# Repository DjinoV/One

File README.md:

# One
 A tiny model rocket flight computer and data logger.
 
 It features:
 - A STM32F103C8T6
 - A BMI088 IMU
 - A BMP280 Barometric pressure sensor
 - A microSD card slot
 - A 32MB flash chip
 - A single pyro channel 
 - Micro USB
 - And ofcourse, a single RGB LED

 Board size:
 50(maybe 40)x30mm
 Powered off a 12V Li-Po

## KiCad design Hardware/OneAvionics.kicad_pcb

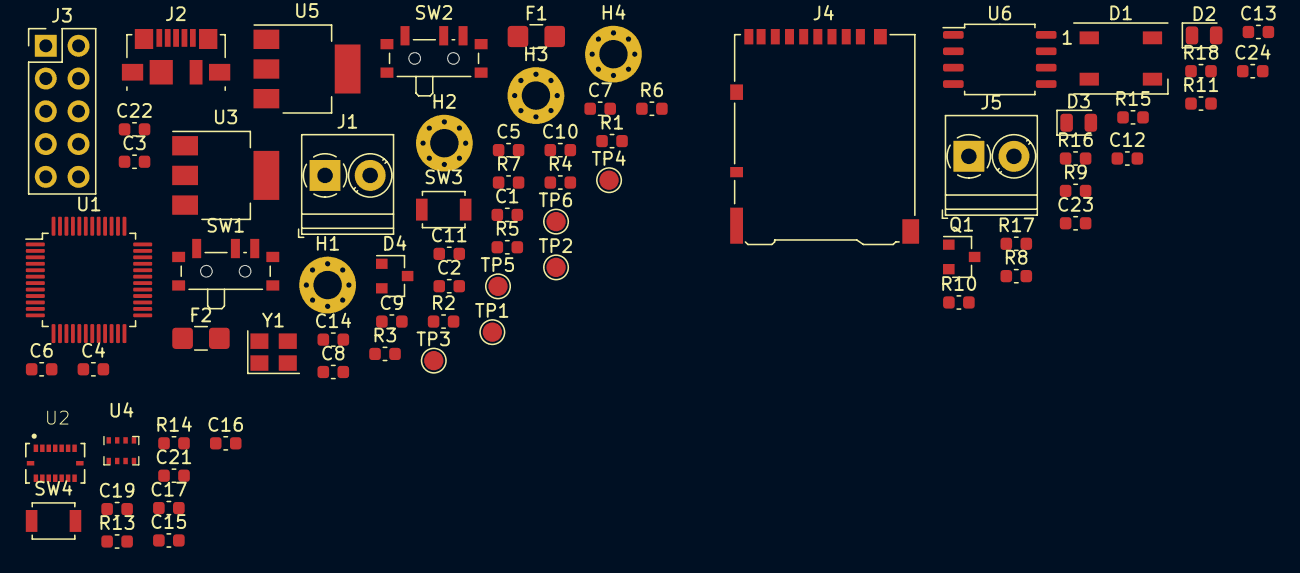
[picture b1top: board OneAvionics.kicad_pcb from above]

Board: 2 copper layers, 72 parts (0 on the bottom side), 37 nets, no tracks yet.

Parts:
C1, C2, C3, C4, C5, C6, C7, C12, C13, C15, C16, C17, C19, C21, C24: 100nF; C_0603_1608Metric
C8, C14: 10uF; C_0603_1608Metric
C9, C22: 0.1uF; C_0603_1608Metric
C10, C11: 22pF; C_0603_1608Metric
C23: 470uF; C_0603_1608Metric
D1: WS2812B; LED_WS2812B_PLCC4_5.0x5.0mm_P3.2mm
D2, D3: LED; LED_0805_2012Metric
D4: D_Schottky; SOT-23
F1, F2: 2A; Fuse_1206_3216Metric_Castellated
H1, H2, H3, H4: MountingHole; MountingHole_2.2mm_M2_Pad_Via
J1: Conn_01x02; TerminalBlock_Phoenix_PT-1,5-2-3.5-H_1x02_P3.50mm_Horizontal
J2: USB_B_Micro; USB_Micro-B_Molex_47346-0001
J3: SWD; PinHeader_2x05_P2.54mm_Vertical
J4: Micro_SD_Card; microSD_HC_Hirose_DM3AT-SF-PEJM5
J5: ST_01x02; TerminalBlock_Phoenix_PT-1,5-2-3.5-H_1x02_P3.50mm_Horizontal
Q1: DMN2230U; SOT-23
R1, R2, R7, R9, R13, R14: 10K; C_0603_1608Metric
R3, R6: 22R; C_0603_1608Metric
R4, R17: 100K; C_0603_1608Metric
R5: 38K; C_0603_1608Metric
R8, R10, R11: 150R; C_0603_1608Metric
R15: 200R; C_0603_1608Metric
R16: 5R; C_0603_1608Metric
R18: 20K; C_0603_1608Metric
SW1, SW2: SW_SPDT; SW_SPDT_PCM12
SW3, SW4: SW_Push; SW_SPST_B3U-1000P
TP1, TP2, TP3, TP4, TP5, TP6: TestPoint; TestPoint_Pad_D1.5mm
U1: STM32F103C8Tx; LQFP-48_7x7mm_P0.5mm
U2: BMI088; PQFN50P450X300X100-16N
U3, U5: LM1117-3.3; SOT-223
U4: BMP280; Bosch_LGA-8_2x2.5mm_P0.65mm_ClockwisePinNumbering
U6: W25Q32JVSS; SOIC-8_5.23x5.23mm_P1.27mm
Y1: 16MHz; Crystal_SMD_3225-4Pin_3.2x2.5mm

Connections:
+3V3: C3.1, C4.1, C5.1, C6.1, C7.1, C9.2, C12.2, C13.2, C15.2, C16.1, C17.2, C19.2, C22.2, C24.2, D1.1, J3.1, J4.4, R7.1, R10.2, R13.1, R14.1, SW1.1, TP3.1, U1.1, U1.9, U1.24, U1.36, U1.48, U2.3, U2.7, U2.11, U2.14, U3.2, U4.2, U4.6, U4.8, U5.2, U6.8
+5V: C1.2, F2.2, J2.1, TP4.1
+12V: F1.2, R4.2, R15.2, SW2.1
/BOOT0: R1.2, TP5.1, U1.44
/BOOT1: R2.2, TP2.1, U1.20
/BUTTON: C21.1, SW4.1, U1.13
/D+: R3.1, U1.32
/D-: R6.1, U1.33
/HSE_IN: C10.1, U1.5, Y1.1
/HSE_OUT: C11.1, U1.6, Y1.3
/LED: R11.2, U1.12
/MISO: J4.7, U1.16, U6.2
/MOSI: J4.3, U1.17, U6.5
/NRST: C2.1, J3.10, R7.2, SW3.1, TP1.1, U1.7
/Output/PYRO_CONT: R17.2, R18.1
/PYRO_1: R8.2, U1.28
/RGB: D1.4, U1.27
/SCK: J4.5, U1.15, U6.6
/SCL: R14.2, U1.42, U2.8, U4.4
/SDA: R13.2, U1.43, U2.9, U4.3
/SWCLK: J3.4, U1.37
/SWDIO: J3.2, U1.34
/VOLTAGE: R4.1, R5.2, U1.29
GND: C1.1, C2.2, C3.2, C4.2, C5.2, C6.2, C7.2, C8.1, C9.1, C10.2, C11.2, C12.1, C13.1, C14.1, C15.1, C16.2, C17.1, C19.1, C21.2, C22.1, C23.1, C24.1, D1.3, D2.1, D3.1, J1.2, J2.5, J2.6, J3.3, J3.5, J3.9, J4.6, J4.9, R2.1, R5.1, R9.2, R16.2, R18.2, SW1.3, SW3.2, SW4.2, TP6.1, U1.8, U1.23, U1.35, U1.47, U2.4, U2.6, U3.1, U4.1, U4.5, U4.7, U5.1, U6.4, Y1.2, Y1.4
unnamed: C8.2, F1.1, U3.3
unnamed: C14.2, F2.1, U5.3
unnamed: C23.2, J5.1, R15.1
unnamed: D2.2, R10.1
unnamed: D3.2, R11.1
unnamed: D4.1, SW2.2
unnamed: D4.2, J1.1
unnamed: J2.2, R6.2
unnamed: J2.3, R3.2
unnamed: J5.2, Q1.3, R17.1
unnamed: Q1.1, R8.1, R9.1
unnamed: Q1.2, R16.1
unnamed: R1.1, SW1.2

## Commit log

2021-03-10 Pyro
2021-03-10 rc and cont on pyro, linear reg, flash
2021-03-10 bno055 removed, bmi088, schotksy
2021-03-10 Update README.md
    yes im very good at engrish
2021-03-13 Schematic cleanup, pyro
    thanks ben for the advice
2021-03-14 more cleanup
2021-03-14 MOAR CLEANUP
2021-03-18 added pdf
2021-03-18 moved readme
